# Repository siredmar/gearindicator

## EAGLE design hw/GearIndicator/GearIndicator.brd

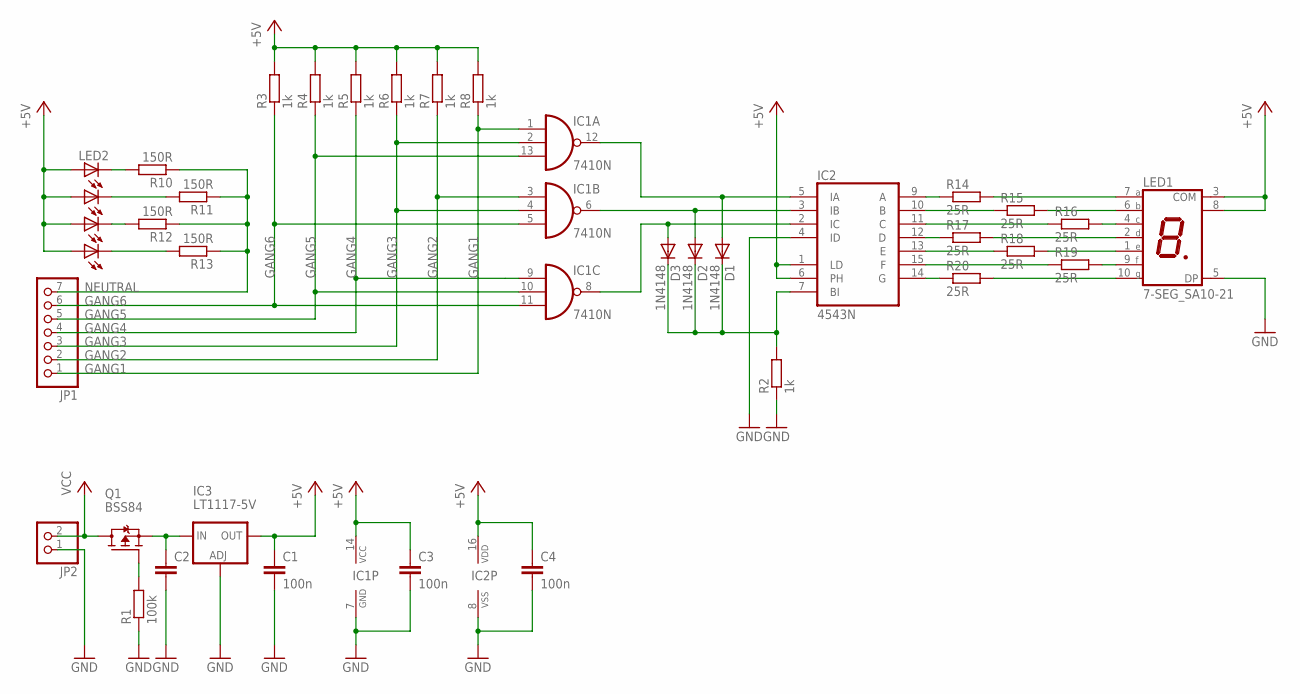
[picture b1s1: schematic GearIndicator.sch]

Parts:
C1, C3, C4: 100n; C0603
C2: C-EUC1206; C1206
D1, D2, D3: 1N4148; SOD80C
IC1: 7410N; DIL14
IC2: 4543N; DIL16
IC3: LT1117-5V; SOT223
JP1: PINHD-1X7/90; 1X07/90
JP2: PINHD-1X2/90; 1X02/90
LED1: 7-SEG_SA10-21; SA10-21
LED2: KB-2755; KB2755
Q1: BSS84; SC75_INFINEON
R1: 100k; R0603
R2, R3, R4, R5, R6, R7, R8: 1k; R0603
R10, R11, R12, R13: 150R; R0603
R14, R15, R16, R17, R18, R19, R20: 25R; R0603

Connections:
+5V: C1.1, C3.1, C4.1, IC1.14 (VCC), IC2.1 (LD), IC2.6 (PH), IC2.16 (VDD), IC3.4 (OUT), LED1.3 (COM), LED1.8 (COM), LED2.2, LED2.3, LED2.6, LED2.7, R3.2, R4.2, R5.2, R6.2, R7.2, R8.2
GANG1: IC1.1 (I0), JP1.1, R8.1
GANG2: IC1.3 (I0), JP1.2, R7.1
GANG3: IC1.2 (I1), IC1.4 (I1), JP1.3, R6.1
GANG4: JP1.4, R5.1
GANG5: IC1.10 (I1), IC1.13 (I2), JP1.5, R4.1
GANG6: IC1.5 (I2), IC1.11 (I2), JP1.6, R3.1
GND: C1.2, C2.2, C3.2, C4.2, IC1.7 (GND), IC2.4 (ID), IC2.8 (VSS), IC3.1 (ADJ), JP2.1, LED1.5 (DP), R1.1, R2.1
unnamed: LED2.8, R10.2
unnamed: LED2.4, R12.2
unnamed: LED2.1, R13.2
unnamed: LED2.5, R11.2
unnamed: IC2.9 (A), R14.1
unnamed: IC2.12 (D), R17.1
unnamed: IC2.14 (G), R20.1
unnamed: Q1.1 (G), R1.2
unnamed: LED1.4 (C), R16.2
unnamed: LED1.9 (F), R19.2
unnamed: LED1.7 (A), R14.2
unnamed: LED1.6 (B), R15.2
unnamed: C2.1, IC3.3 (IN), Q1.3 (S)
unnamed: IC2.10 (B), R15.1
unnamed: IC2.11 (C), R16.1
unnamed: LED1.2 (D), R17.2
unnamed: LED1.1 (E), R18.2
unnamed: IC2.13 (E), R18.1
unnamed: IC2.15 (F), R19.1
unnamed: LED1.10 (G), R20.2
unnamed: D1.A, IC1.12 (O), IC2.5 (IA)
unnamed: D2.A, IC1.6 (O), IC2.3 (IB)
unnamed: D3.A, IC1.8 (O), IC2.2 (IC)
unnamed: D1.C, D2.C, D3.C, IC2.7 (BI), R2.2
NEUTRAL: JP1.7, R10.1, R11.1, R12.1, R13.1
VCC: JP2.2, Q1.2 (D)

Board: 2 copper layers, 34 parts (0 on the bottom side), 34 nets, no tracks yet.

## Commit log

2014-10-15 first version of schematic
